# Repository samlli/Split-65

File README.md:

# split_65
split_65 (insert creative name here) is a split, 65% layout keyboard designed for improved ergonomics and typing comfort over extended periods of time.

<figure>
  
  <figcaption><i>maybe grey's not your taste - red and green and blue, oh my!</i></figcaption>
</figure>

It aims to remain loyal to the standard ansi layout, making the split_65 second nature to use.  The sturdy two part aluminum construction ensures that the keyboard will survive whatever torture is thrown at it over the years

<figure>
  
  <figcaption><i>feels right at home on any desk</i></figcaption>
</figure>

## technical details

<figure>
  
  <figcaption><i>I just wanted to show off an exploded view</i></figcaption>
</figure>

Possible layouts are shown below - the pcb offers stepped caps lock, tsangan, and split backspace support, and users are free to mix and match layouts as needed to suit their needs.

<figure>
  
  <figcaption><i>possible layout one</i></figcaption>
</figure>

<figure>
  
  <figcaption><i>possible layout two</i></figcaption>
</figure>

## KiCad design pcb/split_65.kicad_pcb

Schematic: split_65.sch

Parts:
C1, C2, C8, C9: 22pF; C_0603_1608Metric
C3, C10: 1uF; C_0603_1608Metric
C4, C5, C6, C11, C12, C13: 0.1uF; C_0603_1608Metric
C7, C14: 10uF; C_0603_1608Metric
D0, D1, D2, D3, D4, D5, D6, D7, D8, D9, D10, D11, D12, D13, D14, D15, D16, D17, D18, D19, D20, D21, D22, D23, D24, D25, D26, D27, D28, D29, D30, D31, D32, D33, D35, D36, D37, D38, D39, D40, D41, D42, D43, D44, D45, D46, D47, D48, D49, D50, D51, D52, D53, D54, D55, D56, D57, D58, D59, D60, D61, D62, D63, D64, D65, D66, D67, D68, D69, D70, D71, D72, D73, D74, D75: SOD-123; D_SOD-123
D34, D76: Schottky; D_SOD-123
F1, F2: 500mA; Fuse_1206_3216Metric
FID1, FID2, FID3, FID4, FID5, FID6: Fiducial; Fiducial_1mm_Dia_2.54mm_Outer_CopperTop
J1, J9: PJ-3200B-4A
J2, J10: AVR-ISP-6; Reset_Pretty-Mask
J3, J4, J5, J6, J7, J8, J11, J12, J13, J14: Breakaway_Tabs; breakaway-mousebites
MX0, MX1, MX2, MX3, MX4, MX5, MX6, MX7, MX8, MX10, MX11, MX12, MX13, MX14, MX15, MX18, MX19, MX20, MX21, MX22, MX23, MX25, MX26, MX27, MX28, MX29, MX30, MX31, MX38, MX39, MX40, MX41, MX42, MX43, MX44, MX46, MX47, MX48, MX49, MX50, MX51, MX52, MX53, MX54, MX56, MX57, MX58, MX59, MX60, MX61, MX62, MX64, MX65, MX66, MX67, MX68, MX69, MX71, MX72, MX80, MX81, MX82: MXOnly-1U-NoLED
MX9, MX55, MX76, MX78: MXOnly-1U-NoLED; MXOnly-1.5U-NoLED
MX16: MXOnly-1U-NoLED; MXOnly-1.25U
MX17: MXOnly-1U-NoLED; MXOnly-1.75U-FLIPPED
MX24, MX63, MX74: MXOnly-1U-NoLED; MXOnly-2.25U-NoLED
MX32, MX33, MX34, MX35, MX75, MX77, MX79: MXOnly-1U-NoLED; MXOnly-1.25U-NoLED
MX36, MX73: MXOnly-1U-NoLED; MXOnly-3U-NoLED
MX37: MXOnly-1U-NoLED; MXOnly-2.75U-NoLED
MX45: MXOnly-1U-NoLED; MXOnly-2U-NoLED
MX70: MXOnly-1U-NoLED; MXOnly-1.75U-NoLED
R8, R9: 4.7k; R_0805_2012Metric
R18: 470; R_0805_2012Metric
R24, R40, R69, R88: 10k; R_0805_2012Metric
R38, R39, R86, R87: 22; R_0805_2012Metric
R41, R42, R89, R90: 5.1k; R_0805_2012Metric
U1, U3: ATmega32U4-AU; TQFP-44_10x10mm_P0.8mm
U2, U4: PRTR5V0U2X; SOT143B
USB1, USB2: HRO-TYPE-C-31-M-12; HRO-TYPE-C-31-M-12-Assembly
Y1, Y2: 16MHz; Crystal_SMD_3225-4Pin_3.2x2.5mm

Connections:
+5V: C4.1, C5.1, C6.1, C7.1, D34.1, J1.4, J2.2, R8.1, R9.1, R40.1, U1.14 (VCC), U1.24 (AVCC), U1.34 (VCC), U1.44 (AVCC)
+5VA: C11.1, C12.1, C13.1, C14.1, D76.1, J9.4, J10.2, U3.14 (VCC), U3.24 (AVCC), U3.34 (VCC), U3.44 (AVCC)
CAPSLOCK: MX16.3, MX17.3, U1.8 (PB0)
COL0: MX0.1, MX8.1, MX15.1, MX23.1, MX30.1, U1.31 (PC6)
COL0-R: MX38.1, MX48.1, MX57.1, MX65.1, MX73.1, MX74.1, U3.28 (PB4)
COL1: MX1.1, MX9.1, MX16.1, MX17.1, MX24.1, MX32.1, U1.29 (PB5)
COL1-R: MX39.1, MX49.1, MX58.1, MX66.1, U3.29 (PB5)
COL2: MX2.1, U1.28 (PB4)
COL2-R: MX40.1, MX50.1, MX59.1, MX67.1, MX75.1, U3.30 (PB6)
COL3: MX3.1, MX10.1, MX18.1, MX25.1, MX31.1, MX33.1, U1.27 (PD7)
COL3-R: MX41.1, MX51.1, MX60.1, MX68.1, MX76.1, MX77.1, U3.31 (PC6)
COL4: MX4.1, MX11.1, MX19.1, MX26.1, MX34.1, MX35.1, U1.26 (PD6)
COL4-R: MX42.1, MX52.1, MX61.1, MX69.1, MX78.1, MX79.1, U3.32 (PC7)
COL5: MX5.1, MX12.1, MX20.1, MX27.1, MX36.1, MX37.1, U1.25 (PD4)
COL5-R: MX43.1, MX53.1, MX62.1, MX70.1, MX80.1, U3.25 (PD4)
COL6: MX6.1, MX13.1, MX21.1, MX28.1, U1.20 (PD2)
COL6-R: MX44.1, MX54.1, U3.26 (PD6)
COL7: MX7.1, MX14.1, MX22.1, MX29.1, U1.21 (PD3)
COL7-R: MX45.1, MX46.1, MX55.1, MX63.1, MX71.1, MX81.1, U3.21 (PD3)
COL8-R: MX47.1, MX56.1, MX64.1, MX72.1, MX82.1, U3.20 (PD2)
D+: R38.1, U1.4 (D+)
D+-R: R86.1, U3.4 (D+)
D-: R39.1, U1.3 (D-)
D--R: R87.1, U3.3 (D-)
GND: C1.2, C2.2, C3.2, C4.2, C5.2, C6.2, C7.2, J1.1, J2.6, R18.2, R24.1, R41.2, R42.2, U1.5 (UGND), U1.15 (GND), U1.23 (GND), U1.35 (GND), U1.43 (GND), U2.1, USB1.1, USB1.12, USB1.13, Y1.2, Y1.4
GNDA: C8.2, C9.2, C10.2, C11.2, C12.2, C13.2, C14.2, J9.1, J10.6, R69.1, R88.1, R89.2, R90.2, U3.5 (UGND), U3.15 (GND), U3.23 (GND), U3.35 (GND), U3.43 (GND), U4.1, USB2.1, USB2.12, USB2.13, Y2.2, Y2.4
HDETECT: R40.2, U1.22 (PD5)
HDETECT-R: R88.2, U3.22 (PD5)
MISO: J2.1, U1.11 (PB3)
MISO-R: J10.1, U3.11 (PB3)
MOSI: J2.4, U1.10 (PB2)
MOSI-R: J10.4, U3.10 (PB2)
unnamed: C1.1, U1.17 (XTAL1), Y1.1
unnamed: C2.1, U1.16 (XTAL2), Y1.3
unnamed: C3.1, U1.6 (UCAP)
unnamed: C8.1, U3.17 (XTAL1), Y2.1
unnamed: C9.1, U3.16 (XTAL2), Y2.3
unnamed: C10.1, U3.6 (UCAP)
unnamed: D0.2, MX0.2
unnamed: D1.2, MX1.2
unnamed: D2.2, MX2.2
unnamed: D3.2, MX3.2
unnamed: D4.2, MX4.2
unnamed: D5.2, MX5.2
unnamed: D6.2, MX6.2
unnamed: D7.2, MX7.2
unnamed: D8.2, MX8.2
unnamed: D9.2, MX9.2
unnamed: D10.2, MX10.2
unnamed: D11.2, MX11.2
unnamed: D12.2, MX12.2
unnamed: D13.2, MX13.2
unnamed: D14.2, MX14.2
unnamed: D15.2, MX15.2
unnamed: D16.2, MX16.2, MX17.2
unnamed: D17.2, MX18.2
unnamed: D18.2, MX19.2
unnamed: D19.2, MX20.2
unnamed: D20.2, MX21.2
unnamed: D21.2, MX22.2
unnamed: D22.2, MX23.2
unnamed: D23.2, MX24.2
unnamed: D24.2, MX25.2
unnamed: D25.2, MX26.2
unnamed: D26.2, MX27.2
unnamed: D27.2, MX28.2
unnamed: D28.2, MX29.2
unnamed: D29.2, MX30.2
unnamed: D30.2, MX32.2
unnamed: D31.2, MX31.2, MX33.2
unnamed: D32.2, MX34.2, MX35.2
unnamed: D33.2, MX36.2, MX37.2
unnamed: D35.2, MX38.2
unnamed: D36.2, MX39.2
unnamed: D37.2, MX40.2
unnamed: D38.2, MX41.2
unnamed: D39.2, MX42.2
unnamed: D40.2, MX43.2
unnamed: D41.2, MX44.2
unnamed: D42.2, MX45.2, MX46.2
unnamed: D43.2, MX47.2
unnamed: D44.2, MX48.2
unnamed: D45.2, MX49.2
unnamed: D46.2, MX50.2
unnamed: D47.2, MX51.2
unnamed: D48.2, MX52.2
unnamed: D49.2, MX53.2
unnamed: D50.2, MX54.2
unnamed: D51.2, MX55.2
unnamed: D52.2, MX56.2
unnamed: D53.2, MX57.2
unnamed: D54.2, MX58.2
unnamed: D55.2, MX59.2
unnamed: D56.2, MX60.2
unnamed: D57.2, MX61.2
unnamed: D58.2, MX62.2
unnamed: D59.2, MX63.2
unnamed: D60.2, MX64.2
unnamed: D61.2, MX65.2
unnamed: D62.2, MX66.2
unnamed: D63.2, MX67.2
unnamed: D64.2, MX68.2
unnamed: D65.2, MX69.2
unnamed: D66.2, MX70.2
unnamed: D67.2, MX71.2
unnamed: D68.2, MX72.2
unnamed: D69.2, MX73.2, MX74.2
unnamed: D70.2, MX75.2
unnamed: D71.2, MX76.2, MX77.2
unnamed: D72.2, MX78.2, MX79.2
unnamed: D73.2, MX80.2
unnamed: D74.2, MX81.2
unnamed: D75.2, MX82.2
unnamed: MX16.4, MX17.4, R18.1
unnamed: R24.2, U1.33 (~HWB~/PE2)
unnamed: R38.2, U2.2, USB1.6, USB1.8
unnamed: R39.2, U2.3, USB1.5, USB1.7
unnamed: R41.1, USB1.10
unnamed: R42.1, USB1.4
unnamed: R69.2, U3.33 (~HWB~/PE2)
unnamed: R86.2, U4.2, USB2.6, USB2.8
unnamed: R87.2, U4.3, USB2.5, USB2.7
unnamed: R89.1, USB2.10
unnamed: R90.1, USB2.4
RESET: J2.5, U1.13 (~RESET)
RESET-R: J10.5, U3.13 (~RESET)
ROW0: D0.1, D1.1, D2.1, D3.1, D4.1, D5.1, D6.1, D7.1, U1.39 (PF4)
ROW0-R: D35.1, D36.1, D37.1, D38.1, D39.1, D40.1, D41.1, D42.1, D43.1, U3.1 (PE6)
ROW1: D8.1, D9.1, D10.1, D11.1, D12.1, D13.1, D14.1, U1.40 (PF1)
ROW1-R: D44.1, D45.1, D46.1, D47.1, D48.1, D49.1, D50.1, D51.1, D52.1, U3.41 (PF0)
ROW2: D15.1, D16.1, D17.1, D18.1, D19.1, D20.1, D21.1, U1.41 (PF0)
ROW2-R: D53.1, D54.1, D55.1, D56.1, D57.1, D58.1, D59.1, D60.1, U3.40 (PF1)
ROW3: D22.1, D23.1, D24.1, D25.1, D26.1, D27.1, D28.1, U1.32 (PC7)
ROW3-R: D61.1, D62.1, D63.1, D64.1, D65.1, D66.1, D67.1, D68.1, U3.36 (PF7)
ROW4: D29.1, D30.1, D31.1, D32.1, D33.1, U1.30 (PB6)
ROW4-R: D69.1, D70.1, D71.1, D72.1, D73.1, D74.1, D75.1, U3.27 (PD7)
SCK: J2.3, U1.9 (PB1)
SCK-R: J10.3, U3.9 (PB1)
SCL: J1.2, R9.2, U1.18 (PD0)
SCL-R: J9.2, U3.18 (PD0)
SDA: J1.3, R8.2, U1.19 (PD1)
SDA-R: J9.3, U3.19 (PD1)
VBUS: D34.2, F1.1, U1.2 (UVCC), U1.7 (VBUS)
VCC: F1.2, U2.4, USB1.2, USB1.11
VDC: D76.2, F2.1, U3.2 (UVCC), U3.7 (VBUS)
VDD: F2.2, U4.4, USB2.2, USB2.11

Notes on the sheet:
ISP Header
TRRS for I2C
MCU
USB, ESD protection, Polyfuse
Resistors on left half only
Switch Matrix
Extra Hardware
LEFT HAND SCHEMATIC
RIGHT HAND SCHEMATIC Power net changes: VCC -> VDD VBUS -> VDC GND -> GNDA +5V -> +5VA to prevent kicad from complaining about no connections between halves
Half Detection
Read low = Right hand
Extras

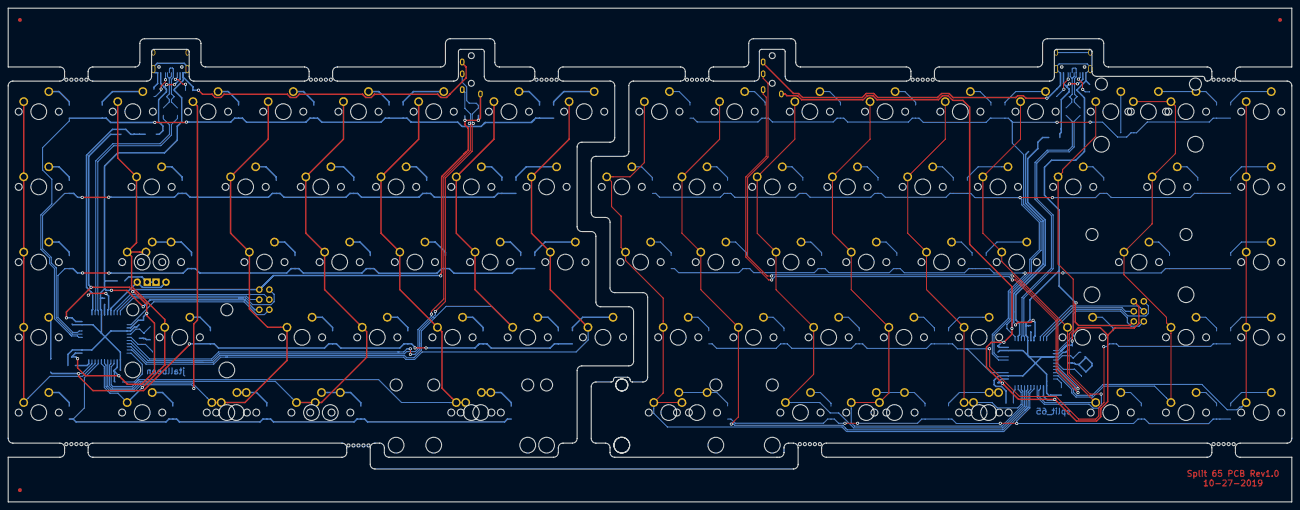
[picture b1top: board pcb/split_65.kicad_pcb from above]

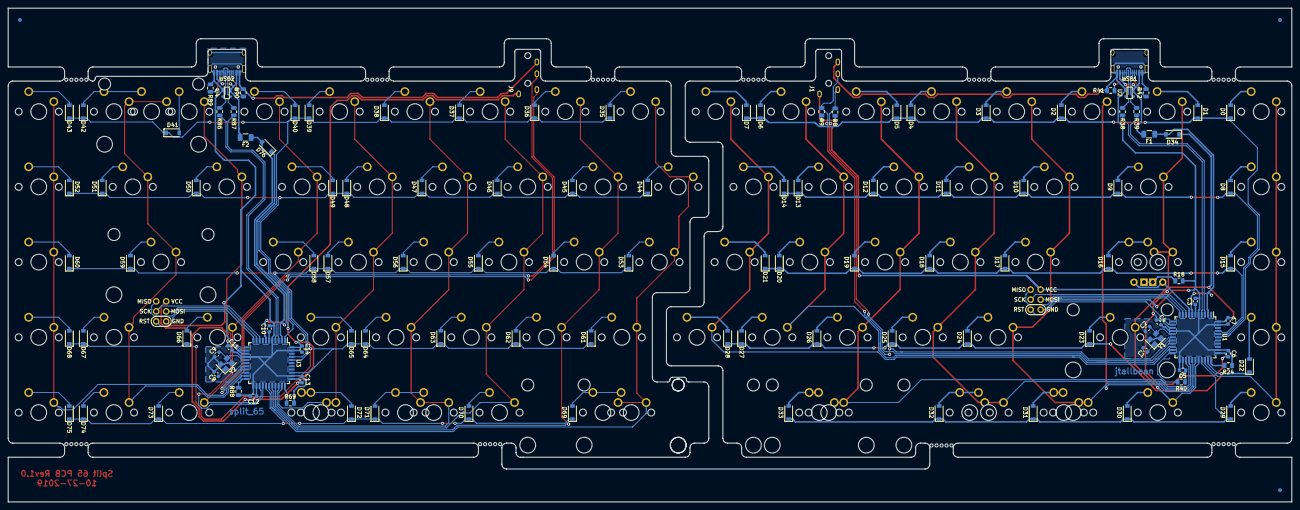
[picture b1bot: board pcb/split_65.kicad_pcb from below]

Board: 2 copper layers, 325.0 x 125.0 mm, 219 parts (133 on the bottom side), 146 nets.

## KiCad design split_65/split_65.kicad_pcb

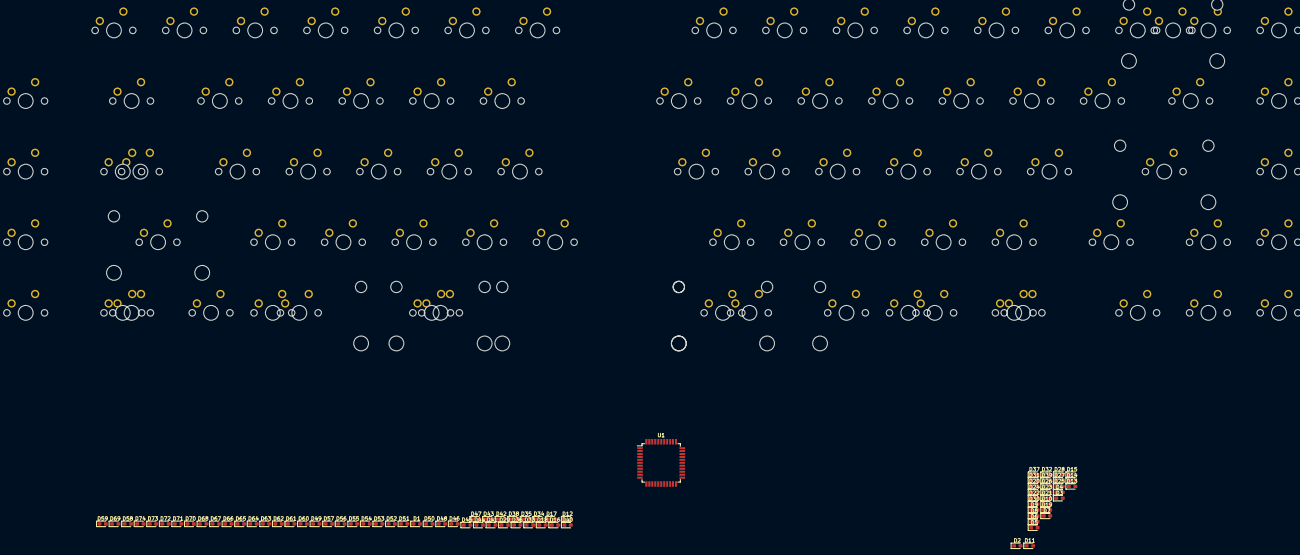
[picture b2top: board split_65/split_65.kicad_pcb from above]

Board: 2 copper layers, 157 parts (0 on the bottom side), 103 nets, no tracks yet.

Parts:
D1, D2, D3, D4, D5, D6, D7, D8, D9, D10, D11, D12, D13, D14, D15, D16, D17, D18, D19, D20, D21, D22, D23, D24, D25, D26, D27, D28, D29, D30, D31, D32, D33, D34, D35, D36, D37, D38, D39, D40, D41, D42, D43, D44, D45, D46, D47, D48, D49, D50, D51, D52, D53, D54, D55, D56, D57, D58, D59, D60, D61, D62, D63, D64, D65, D66, D67, D68, D69, D70, D71, D72, D73, D74: D_Small; D_0603_1608Metric_Pad1.05x0.95mm_HandSolder
SW1, SW2, SW3, SW4, SW5, SW6, SW13, SW14, SW15, SW16, SW19, SW20, SW21, SW22, SW24, SW25, SW26, SW27, SW30, SW31, SW32, SW33, SW34, SW35, SW36, SW37, SW38, SW39, SW40, SW41, SW44, SW45, SW46, SW47, SW48, SW49, SW50, SW51, SW53, SW54, SW55, SW56, SW59, SW60, SW61, SW62, SW65, SW66, SW67, SW69, SW70, SW71, SW72, SW76, SW77, SW78, SW79, SW80, SW81, SW82: SW_Push; MXOnly-1U-NoLED
SW7, SW12, SW18, SW58, SW64, SW74: SW_Push; MXOnly-1.5U-NoLED
SW8, SW68: SW_Push; MXOnly-1.75U-NoLED
SW9, SW11, SW17, SW23, SW52, SW57, SW63: SW_Push; MXOnly-1.25U-NoLED
SW10, SW42, SW75: SW_Push; MXOnly-2.25U-NoLED
SW28: SW_Push; MXOnly-2.75U-NoLED
SW29, SW43: SW_Push; MXOnly-3U-NoLED
SW73: SW_Push; MXOnly-2U-NoLED
U1: ATmega32U4-AU; TQFP-44_10x10mm_P0.8mm

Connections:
unnamed: D1.1, D6.1, D11.1, D16.1, D21.1, D26.1, D30.1
unnamed: D1.2, SW1.1
unnamed: D2.2, SW2.1
unnamed: D3.2, SW3.1
unnamed: D4.2, SW4.1
unnamed: D5.2, SW5.1
unnamed: D6.2, SW6.1
unnamed: D7.2, SW7.1
unnamed: D8.2, SW8.1, SW9.1
unnamed: D9.2, SW10.1
unnamed: D5.1, D10.1, D15.1, D20.1, D25.1
unnamed: D10.2, SW11.1, SW12.1
unnamed: D11.2, SW13.1
unnamed: D2.1, D7.1, D12.1, D17.1, D22.1, D27.1, D31.1
unnamed: D12.2, SW14.1
unnamed: D3.1, D8.1, D13.1, D18.1, D23.1, D28.1, D32.1
unnamed: D13.2, SW15.1
unnamed: D4.1, D9.1, D14.1, D19.1, D24.1, D29.1, D33.1
unnamed: D14.2, SW16.1
unnamed: D15.2, SW17.1, SW18.1
unnamed: D16.2, SW19.1
unnamed: D17.2, SW20.1
unnamed: D18.2, SW21.1
unnamed: D19.2, SW22.1
unnamed: D20.2, SW23.1
unnamed: D21.2, SW24.1
unnamed: D22.2, SW25.1
unnamed: D23.2, SW26.1
unnamed: D24.2, SW27.1
unnamed: D25.2, SW28.1, SW29.1
unnamed: D26.2, SW30.1
unnamed: D27.2, SW31.1
unnamed: D28.2, SW32.1
unnamed: D29.2, SW33.1
unnamed: D30.2, SW34.1
unnamed: D31.2, SW35.1
unnamed: D32.2, SW36.1
unnamed: D33.2, SW37.1
unnamed: D34.1, D39.1, D43.1, D48.1, D53.1, D58.1, D63.1, D65.1, D70.1
unnamed: D34.2, SW38.1
unnamed: D35.1, D40.1, D44.1, D49.1, D54.1, D59.1, D64.1, D66.1, D71.1
unnamed: D35.2, SW39.1
unnamed: D36.1, D41.1, D45.1, D50.1, D55.1, D60.1, D67.1, D72.1
unnamed: D36.2, SW40.1
unnamed: D37.1, D42.1, D46.1, D51.1, D56.1, D61.1, D68.1, D73.1
unnamed: D37.2, SW41.1
unnamed: D38.1, D47.1, D52.1, D57.1, D62.1, D69.1, D74.1
unnamed: D38.2, SW42.1, SW43.1
unnamed: D39.2, SW44.1
unnamed: D40.2, SW45.1
unnamed: D41.2, SW46.1
unnamed: D42.2, SW47.1
unnamed: D43.2, SW48.1
unnamed: D44.2, SW49.1
unnamed: D45.2, SW50.1
unnamed: D46.2, SW51.1
unnamed: D47.2, SW52.1
unnamed: D48.2, SW53.1
unnamed: D49.2, SW54.1
unnamed: D50.2, SW55.1
unnamed: D51.2, SW56.1
unnamed: D52.2, SW57.1, SW58.1
unnamed: D53.2, SW59.1
unnamed: D54.2, SW60.1
unnamed: D55.2, SW61.1
unnamed: D56.2, SW62.1
unnamed: D57.2, SW63.1, SW64.1
unnamed: D58.2, SW65.1
unnamed: D59.2, SW66.1
unnamed: D60.2, SW67.1
unnamed: D61.2, SW68.1
unnamed: D62.2, SW69.1
unnamed: D63.2, SW70.1
unnamed: D64.2, SW71.1
unnamed: D65.2, SW72.1, SW73.1
unnamed: D66.2, SW74.1
unnamed: D67.2, SW75.1
unnamed: D68.2, SW76.1
unnamed: D69.2, SW77.1
unnamed: D70.2, SW78.1
unnamed: D71.2, SW79.1
unnamed: D72.2, SW80.1
unnamed: D73.2, SW81.1
unnamed: D74.2, SW82.1
unnamed: SW1.2, SW2.2, SW3.2, SW4.2, SW5.2
unnamed: SW6.2, SW7.2, SW8.2, SW9.2, SW10.2, SW11.2, SW12.2
unnamed: SW13.2, SW14.2, SW15.2, SW16.2, SW17.2, SW18.2
unnamed: SW19.2, SW20.2, SW21.2, SW22.2, SW23.2
unnamed: SW24.2, SW25.2, SW26.2, SW27.2, SW28.2, SW29.2
unnamed: SW30.2, SW31.2, SW32.2, SW33.2
unnamed: SW34.2, SW35.2, SW36.2, SW37.2
unnamed: SW38.2, SW39.2, SW40.2, SW41.2, SW42.2, SW43.2
unnamed: SW44.2, SW45.2, SW46.2, SW47.2
unnamed: SW48.2, SW49.2, SW50.2, SW51.2, SW52.2
unnamed: SW53.2, SW54.2, SW55.2, SW56.2, SW57.2, SW58.2
unnamed: SW59.2, SW60.2, SW61.2, SW62.2, SW63.2, SW64.2
unnamed: SW65.2, SW66.2, SW67.2, SW68.2, SW69.2
unnamed: SW70.2, SW71.2
unnamed: SW72.2, SW73.2, SW74.2, SW75.2, SW76.2, SW77.2
unnamed: SW78.2, SW79.2, SW80.2, SW81.2, SW82.2
unnamed: U1.14, U1.34
unnamed: U1.15, U1.23, U1.35, U1.43
unnamed: U1.24, U1.44

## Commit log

2018-10-21 added kle
2018-10-21 begin pcb schematic
2018-11-18 switches, diodes schematic
2018-11-19 assigned fp and pcbnew layout for switches
2018-11-20 setup schematic hierarchies, update images
2019-01-05 add cool renders, complete pcb schematic
2019-01-05 increased spacing
2019-01-05 fixed bolding
2019-01-08 laid out diodes and resistors
2019-01-12 did edge cuts
2019-01-13 edge cuts, route usb
2019-01-22 add switch, edit models
2019-01-27 add resistor to rst, rgb underglow
2019-01-30 added rgb underglow and step files
2019-02-01 more traces
2019-02-02 generated step files
2019-02-04 moved usb/trrs port closer in
2019-02-23 break out mcu pins
2019-03-18 added more renders, changed pcb layout
2019-03-21 pdf of schematic
2019-04-10 reset layouts
2019-04-10 laid out ws2812b
2019-05-16 removed underglow and backlight, routed left hand
2019-05-17 routed right hand side
2019-05-17 added step files, combined and panelized
2019-10-20 update pcb traces
2019-10-27 update silkscreen
2020-01-10 Added BOM, gerbers, and position
